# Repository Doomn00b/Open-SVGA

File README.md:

# Open-SVGA
Video-card and GPU for the PC x86 platform, including PCB reference-design

This project is meant to encompass a PCI 3.0 31-bits video-card capable of displaying the majority of resolutions and video-modes from CGA, EGA, VGA and finally SVGA. Drivers are meant to be developed for DoS 6.5, Windows 98SE and Windows 10.

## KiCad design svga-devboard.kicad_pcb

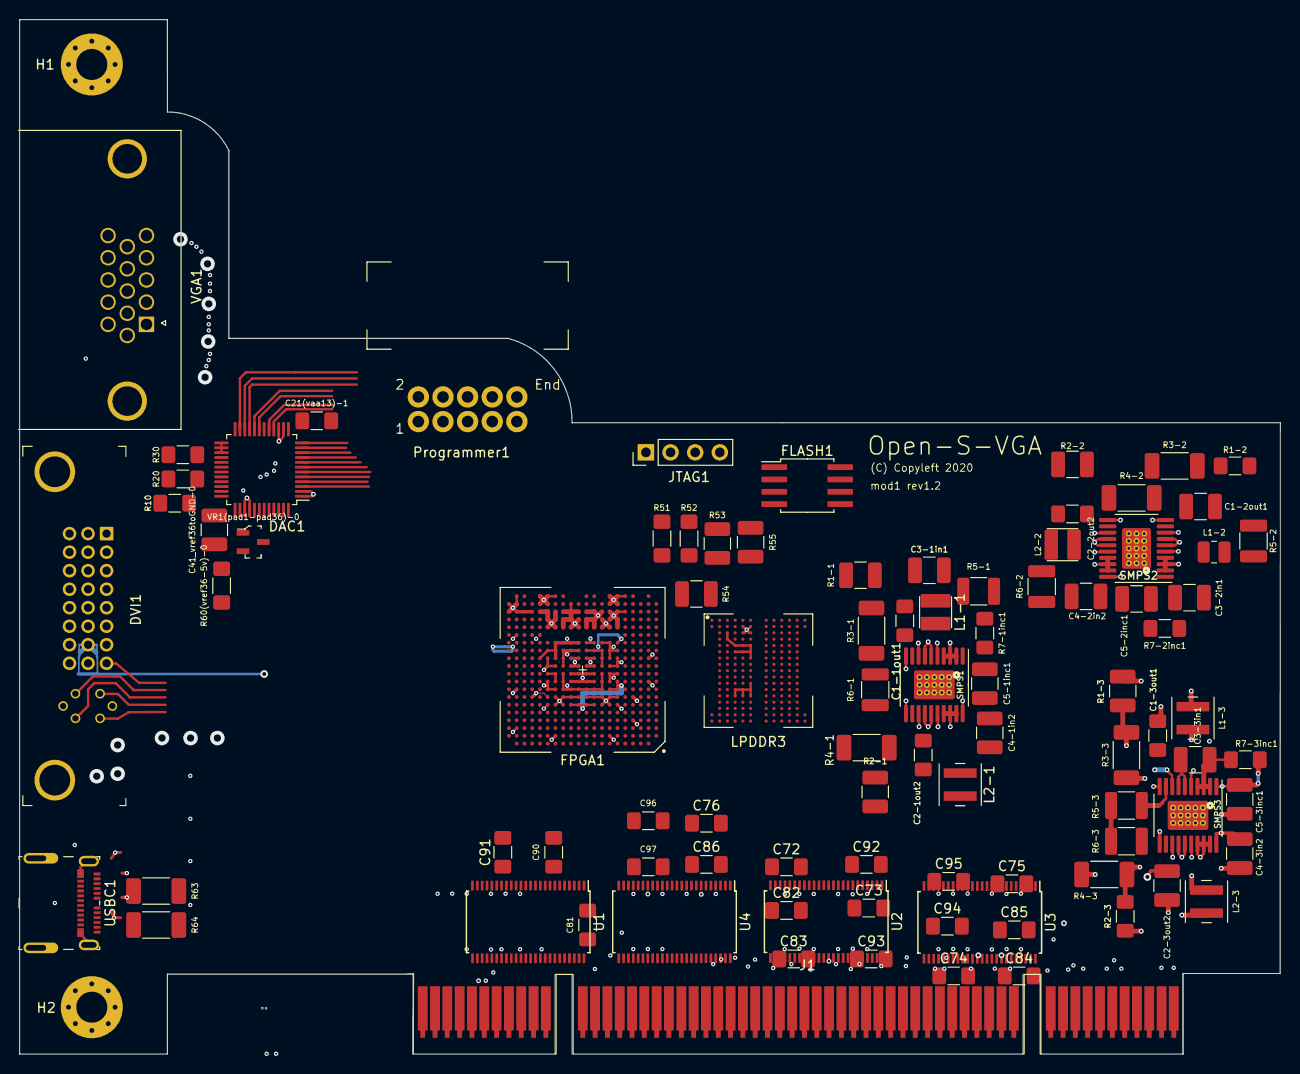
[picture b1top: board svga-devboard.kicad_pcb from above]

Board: 4 copper layers, 130.0 x 106.7 mm, 106 parts (0 on the bottom side), 146 nets.

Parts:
C1-1out1, C1-3out1, C2-1out2, C2-2out2: C3216X7S0J336M160AC; C_1206_3216Metric_Pad1.42x1.75mm_HandSolder
C1-2out1, C2-3out2: C3225X7R1C226M250AC; C_1210_3225Metric_Pad1.42x2.65mm_HandSolder
C3-1in1, C3-2in1, C3-3in1, C4-1in2, C4-2in2, C4-3in2, C41_vref36toGND-0: C1210C156K8PACTU; C_1210_3225Metric_Pad1.42x2.65mm_HandSolder
C5-1inc1, C5-2inc1, C5-3inc1: C1210C474K5RACTU; C_1210_3225Metric_Pad1.42x2.65mm_HandSolder
C10(vaa29)-0, C20(vaa13)-0, C30(vaa30)-0, C42(+5to35)1, C80, C81, C82, C83, C84, C85, C86, C87, C90, C91, C92, C93, C94, C95, C96, C97: VJ1206Y104JXAAR; C_1206_3216Metric_Pad1.42x1.75mm_HandSolder
C11(vaa29)-1, C21(vaa13)-1, C31(vaa30)-1: VJ1206Y103JXAMC; C_1206_3216Metric_Pad1.42x1.75mm_HandSolder
C70, C71, C72, C73, C74, C75, C76, C77: C1206C105K4RACTU; C_1206_3216Metric_Pad1.42x1.75mm_HandSolder
DAC1: ADV7125KSTZ50; LQFP-48_7x7mm_P0.5mm
DVI1: 74320-9010; DVI_Female_74320-9010
FLASH1: ISSI_IS25WP128F-JBLE; SOIC-8_5.28x5.28mm_P1.27mm
FPGA1: LFE5U-85F-BG381-LRJ; caBGA-381_15.2x15.2_17.0x17.0mm
H1, H2: MountingHole_Pad; MountingHole_3.2mm_M3_Pad_Via
J1: Bus_PCI_32bit_Universal_lrj; BUS_PCI_UNI_32-lrj2
JTAG1: CONN_04JST-PTH; PinHeader_1x04_P2.54mm_Vertical
L1-1, L2-2: VLS3015CX-1R5M-1; L_TDK_VLS3015CX-1_handsoldering
L1-2: 1008PS-152KLC; L_1008_2520Metric
L1-3, L2-1, L2-3: XFL4015-701MEC; L_Coilcraft_XFL4015
LPDDR3: W63CH2MBVACE; Winbond_VFBGA-178_W63CH2MBVACE
Programmer1: Wurth_WR-BHD_61201021721; WE_WR-BHD_RA_2x5_P2.54mm_Drill1.2mm
R1-1: CRCW121012K7FKEA; R_1210_3225Metric_Pad1.42x2.65mm_HandSolder
R1-2: ERJ-8ENF2152V; R_1206_3216Metric_Pad1.42x1.75mm_HandSolder
R1-3, R2-1: ERJ-14NF3741U; R_1210_3225Metric_Pad1.42x2.65mm_HandSolder
R2-2: RC1210FR-074K99L; R_1210_3225Metric_Pad1.42x2.65mm_HandSolder
R2-3, R7-1inc1, R7-2inc1, R7-3inc1: CRCW12064R99FKEAHP; R_1206_3216Metric_Pad1.42x1.75mm_HandSolder
R3-1, R3-2, R3-3, R4-1, R4-2, R4-3: CMP2010-FX-1002ELF; R_2010_5025Metric_Pad1.52x2.65mm_HandSolder
R5-1, R5-2, R5-3, R6-1, R6-2, R6-3: RC1210FR-0749K9L; R_YAGEO_1210_3225Metric_HandSolder
R10, R20, R30: CRCW120675R0FKEA; R_1206_3216Metric_Pad1.42x1.75mm_HandSolder
R51, R52: ERJ-8ENF4701V; R_Panasonic_1206_3216Metric_ERJ8EN_HandSolder
R53, R55: ERJ-14YJ103U; R_1210_3225Metric_Pad1.42x2.65mm_HandSolder
R54: RC1210FR-071KL; R_1210_3225Metric_Pad1.42x2.65mm_HandSolder
R60(vref36-5v)-0: ERJ-8ENF1001V; R_Panasonic_1206_3216Metric_ERJ8EN_HandSolder
R63, R64: CMP2010-FX-1004ELF; R_2010_5025Metric_Pad1.52x2.65mm_HandSolder
RZQ1: ERJ-8ENF2400V; R_Panasonic_1206_3216Metric_ERJ8EN_HandSolder
SMPS1, SMPS2, SMPS3: LM26420-Q1MHX_NOPB; HTSSOP-20-1EP_4.4x6.5mm_P0.42mm_EP3.2x6.4mm_Mask3.0x4.2mm_T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
U1, U2, U3, U4: SN74LVCH16T245DGGR; TSSOP-48_6.1x12.5mm_P0.5mm
USBC1: USB_C_Molex_201267-0005; USB-C_Receptacle_2012670005
VGA1: Amphenol_L77HDE15SD1CH4RHNVGA; DSUB-Amphenol_L77HDE15SD1CH4RHNVGA
VR1(pad1-pad36)-0: AD1580ARTZ-REEL7; SOT-23-3

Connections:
+0V8: C2-3out2.1, FPGA1.D20, L2-3.2, R2-3.2
+1V1: C1-3out1.1, C2-1out2.1, FPGA1.H8, FPGA1.H9, FPGA1.H10, FPGA1.H11, FPGA1.H12, FPGA1.H13, FPGA1.J8, FPGA1.J13, FPGA1.K8, FPGA1.K13, FPGA1.L8, FPGA1.L13, FPGA1.M8, FPGA1.M13, FPGA1.N8, FPGA1.N9, FPGA1.N10, FPGA1.N11, FPGA1.N12, FPGA1.N13, L1-3.1, L2-1.2, R1-3.1, R2-1.2
+1V2: C2-2out2.1, C90.1, C91.1, C92.1, C93.1, C94.1, C95.1, C96.1, C97.1, L2-2.2, LPDDR3.A8, LPDDR3.A9, LPDDR3.A11, LPDDR3.C12, LPDDR3.D4, LPDDR3.D5, LPDDR3.D6, LPDDR3.E8, LPDDR3.E12, LPDDR3.F2, LPDDR3.G2, LPDDR3.G5, LPDDR3.G12, LPDDR3.H3, LPDDR3.H5, LPDDR3.H6, LPDDR3.H8, LPDDR3.H9, LPDDR3.H11, LPDDR3.H12, LPDDR3.J5, LPDDR3.J6, LPDDR3.J9, LPDDR3.J10, LPDDR3.K5, LPDDR3.K6, LPDDR3.K8, LPDDR3.K11, LPDDR3.K12, LPDDR3.L2, LPDDR3.L5, LPDDR3.L12, LPDDR3.M2, LPDDR3.N8, LPDDR3.N12, LPDDR3.P4, LPDDR3.P5, LPDDR3.P6, LPDDR3.R12, LPDDR3.U8, LPDDR3.U9, LPDDR3.U11, R2-2.2, U1.7, U1.18, U2.7, U2.18, U3.7, U3.18, U4.7, U4.18
+1V8: C1-1out1.1, FLASH1.8, L1-1.1, LPDDR3.A3, LPDDR3.A4, LPDDR3.A5, LPDDR3.A6, LPDDR3.A10, LPDDR3.U3, LPDDR3.U4, LPDDR3.U5, LPDDR3.U6, LPDDR3.U10, R1-1.1
+2V5: C1-2out1.1, FLASH1.6, FPGA1.F6, FPGA1.F9, FPGA1.F10, FPGA1.F11, FPGA1.F12, FPGA1.F15, FPGA1.H6, FPGA1.H7, FPGA1.H14, FPGA1.H15, FPGA1.J6, FPGA1.J15, FPGA1.L6, FPGA1.L7, FPGA1.L14, FPGA1.L15, FPGA1.M6, FPGA1.M15, FPGA1.P6, FPGA1.P9, FPGA1.P10, FPGA1.T4, FPGA1.U3, L1-2.1, Programmer1.10, R1-2.1, R52.2, R53.2, R54.1, R54.2, R55.2, R64.2
+3V3: C3-1in1.2, C4-1in2.2, C4-2in2.2, C71.2, C73.2, C75.2, C77.2, C81.1, C83.1, C85.1, C87.1, J1.A21, J1.A27, J1.A33, J1.A39, J1.A45, J1.A53, J1.B25, J1.B31, J1.B36, J1.B41, J1.B43, J1.B54, R5-1.1, R6-1.1, R6-2.1, R7-1inc1.2, SMPS1.2, SMPS1.3, SMPS1.4, SMPS1.17, SMPS1.18, SMPS1.19, SMPS2.17, SMPS2.18, SMPS2.19, U1.42, U2.42, U3.42, U4.42
+5V: C3-2in1.2, C3-3in1.2, C4-3in2.2, C10(vaa29)-0.1, C11(vaa29)-1.1, C20(vaa13)-0.1, C21(vaa13)-1.1, C30(vaa30)-0.1, C31(vaa30)-1.1, C42(+5to35)1.1, C70.2, C72.2, C74.2, C76.2, C80.1, C82.1, C84.1, C86.1, DAC1.13, DAC1.29, DAC1.30, DVI1.14, J1.A5, J1.A8, J1.A61, J1.A62, J1.B5, J1.B6, J1.B61, J1.B62, R5-2.1, R5-3.1, R6-3.1, R7-2inc1.2, R7-3inc1.2, R60(vref36-5v)-0.1, SMPS2.2, SMPS2.3, SMPS2.4, SMPS3.2, SMPS3.3, SMPS3.4, SMPS3.17, SMPS3.18, SMPS3.19, U1.31, U2.31, U3.31, U4.31, USBC1.A4, USBC1.A9, USBC1.B4, USBC1.B9, VGA1.9
/DAC/ABLUE: DAC1.28, R30.2
/DAC/AGREEN: DAC1.32, R20.2
/DAC/ARED: DAC1.34, R10.2
/DAC/BLANK_DAC: DAC1.11, FPGA1.L18
/DAC/BLUE0: DAC1.16, FPGA1.P17
/DAC/BLUE1: DAC1.17, FPGA1.J16
/DAC/BLUE2: DAC1.18, FPGA1.T16
/DAC/BLUE3: DAC1.19, FPGA1.F16
/DAC/BLUE4: DAC1.20, FPGA1.U19
/DAC/BLUE5: DAC1.21, FPGA1.J18
/DAC/BLUE6: DAC1.22, FPGA1.H16
/DAC/BLUE7: DAC1.23, FPGA1.G16
/DAC/CLK_DAC: DAC1.24, FPGA1.P20
/DAC/GREEN0: DAC1.3, FPGA1.R17
/DAC/GREEN1: DAC1.4, FPGA1.R16
/DAC/GREEN2: DAC1.5, FPGA1.P19
/DAC/GREEN3: DAC1.6, FPGA1.P18
/DAC/GREEN4: DAC1.7, FPGA1.T18
/DAC/GREEN5: DAC1.8, FPGA1.K18
/DAC/GREEN6: DAC1.9, FPGA1.N18
/DAC/GREEN7: DAC1.10, FPGA1.U20
/DAC/RED0: DAC1.41, FPGA1.R20
/DAC/RED1: DAC1.42, FPGA1.E18
/DAC/RED2: DAC1.43, FPGA1.J17
/DAC/RED3: DAC1.44, FPGA1.J20
/DAC/RED4: DAC1.45, FPGA1.F18
/DAC/RED5: DAC1.46, FPGA1.F20
/DAC/RED6: DAC1.47, FPGA1.E16
/DAC/RED7: DAC1.48, FPGA1.K20
/DAC/SYNC_DAC: DAC1.12, FPGA1.E20
/DRAM/A0_DRAM: FPGA1.G5, LPDDR3.R2
/DRAM/A1_DRAM: FPGA1.C2, LPDDR3.P2
/DRAM/A2_DRAM: FPGA1.C3, LPDDR3.N2
/DRAM/A3_DRAM: FPGA1.B5, LPDDR3.N3
/DRAM/A4_DRAM: FPGA1.C5, LPDDR3.M3
/DRAM/A5_DRAM: FPGA1.J3, LPDDR3.F3
/DRAM/A6_DRAM: FPGA1.H3, LPDDR3.E3
/DRAM/A7_DRAM: FPGA1.G1, LPDDR3.E2
/DRAM/A8_DRAM: FPGA1.E5, LPDDR3.D2
/DRAM/A9_DRAM: FPGA1.F5, LPDDR3.C2
/DRAM/CKE_DRAM: FPGA1.H4, LPDDR3.K3
/DRAM/CK_t_DRAM: FPGA1.G3, LPDDR3.J3
/DRAM/D0_DRAM: FPGA1.M1, LPDDR3.P9
/DRAM/D1_DRAM: FPGA1.K2, LPDDR3.N9
/DRAM/D2_DRAM: FPGA1.M5, LPDDR3.N10
/DRAM/D3_DRAM: FPGA1.M3, LPDDR3.N11
/DRAM/D4_DRAM: FPGA1.J1, LPDDR3.M8
/DRAM/D5_DRAM: FPGA1.K5, LPDDR3.M9
/DRAM/D6_DRAM: FPGA1.K4, LPDDR3.M10
/DRAM/D7_DRAM: FPGA1.N3, LPDDR3.M11
/DRAM/D8_DRAM: FPGA1.P4, LPDDR3.F11
/DRAM/D9_DRAM: FPGA1.D2, LPDDR3.F10
/DRAM/D10_DRAM: FPGA1.D3, LPDDR3.F9
/DRAM/D11_DRAM: FPGA1.N2, LPDDR3.F8
/DRAM/D12_DRAM: FPGA1.P3, LPDDR3.E11
/DRAM/D13_DRAM: FPGA1.K1, LPDDR3.E10
/DRAM/D14_DRAM: FPGA1.L1, LPDDR3.E9
/DRAM/D15_DRAM: FPGA1.N1, LPDDR3.D9
/DRAM/D16_DRAM: FPGA1.E2, LPDDR3.T8
/DRAM/D17_DRAM: FPGA1.A3, LPDDR3.T9
/DRAM/D18_DRAM: FPGA1.E1, LPDDR3.T10
/DRAM/D19_DRAM: FPGA1.F2, LPDDR3.T11
/DRAM/D20_DRAM: FPGA1.H2, LPDDR3.R8
/DRAM/D21_DRAM: FPGA1.B3, LPDDR3.R9
/DRAM/D22_DRAM: FPGA1.B2, LPDDR3.R10
/DRAM/D23_DRAM: FPGA1.H1, LPDDR3.R11
/DRAM/D24_DRAM: FPGA1.L2, LPDDR3.C11
/DRAM/D25_DRAM: FPGA1.L3, LPDDR3.C10
/DRAM/D26_DRAM: FPGA1.N4, LPDDR3.C9
/DRAM/D27_DRAM: FPGA1.P5, LPDDR3.C8
/DRAM/D28_DRAM: FPGA1.H5, LPDDR3.B11
/DRAM/D29_DRAM: FPGA1.K3, LPDDR3.B10
/DRAM/D30_DRAM: FPGA1.L5, LPDDR3.B9
/DRAM/D31_DRAM: FPGA1.L4, LPDDR3.B8
/DRAM/DM0_DRAM: FPGA1.P1, LPDDR3.L8
/DRAM/DM1_DRAM: FPGA1.P2, LPDDR3.G8
/DRAM/DM2_DRAM: FPGA1.J4, LPDDR3.P8
/DRAM/DM3_DRAM: FPGA1.J5, LPDDR3.D8
/DRAM/DQS0c_DRAM: FPGA1.A5, LPDDR3.L11
/DRAM/DQS0t_DRAM: FPGA1.A4, LPDDR3.L10
/DRAM/DQS1c_DRAM: FPGA1.D1, LPDDR3.G11
/DRAM/DQS1t_DRAM: FPGA1.C1, LPDDR3.G10
/DRAM/DQS2c_DRAM: FPGA1.N5, LPDDR3.P11
/DRAM/DQS2t_DRAM: FPGA1.M4, LPDDR3.P10
/DRAM/DQS3c_DRAM: FPGA1.F1, LPDDR3.D11
/DRAM/DQS3t_DRAM: FPGA1.G2, LPDDR3.D10
/JTAG+Config/CSSPIN_FPGA: FLASH1.1, FPGA1.R2, Programmer1.7, R52.1
/JTAG+Config/DOUT_FPGA: FPGA1.R3, Programmer1.5
/JTAG+Config/INIT_FPGA: FPGA1.V3, Programmer1.3
/JTAG+Config/IO2_FPGA: FLASH1.3, FPGA1.Y2, Programmer1.6
/JTAG+Config/IO3_FPGA: FLASH1.7, FPGA1.W1, Programmer1.8
/JTAG+Config/MISO_FPGA: FLASH1.2, FPGA1.V2, Programmer1.4, R55.1
/JTAG+Config/MOSI_FPGA: FLASH1.5, FPGA1.W2, Programmer1.2, R53.1
/JTAG+Config/PROG_FPGA: FPGA1.W3, Programmer1.1
/JTAG+Config/TCK_FPGA: FPGA1.T5, JTAG1.1, R51.2
/JTAG+Config/TDI_FPGA: FPGA1.R5, JTAG1.2
/JTAG+Config/TDO_FPGA: FPGA1.V4, JTAG1.3
/JTAG+Config/TMS_FPGA: FPGA1.U5, JTAG1.4
/VGA + DVI + USBC/ABLUE: DVI1.C3, VGA1.3
/VGA + DVI + USBC/AGREEN: DVI1.C2, VGA1.2
/VGA + DVI + USBC/ARED: DVI1.C1, VGA1.1
/VGA + DVI + USBC/AUX+: R64.1, USBC1.A8
/VGA + DVI + USBC/AUX-: R63.1, USBC1.B8
/VGA + DVI + USBC/DBLUE+2: DVI1.13, USBC1.A11
/VGA + DVI + USBC/DBLUE-2: DVI1.12, USBC1.A10
/VGA + DVI + USBC/DDC-C_ID3: DVI1.6, VGA1.15
/VGA + DVI + USBC/DDC-D_ID1: DVI1.7, VGA1.12
/VGA + DVI + USBC/DGREEN+2: DVI1.5, USBC1.A2
/VGA + DVI + USBC/DGREEN-2: DVI1.4, USBC1.A3
/VGA + DVI + USBC/DRED+2: DVI1.21, USBC1.B11
/VGA + DVI + USBC/DRED-2: DVI1.20, USBC1.B10
/VGA + DVI + USBC/Hsync_A: DVI1.C4, VGA1.14
/VGA + DVI + USBC/Vsync_A: DVI1.8, VGA1.13
GND: C1-1out1.2, C1-2out1.2, C1-3out1.2, C2-1out2.2, C2-2out2.2, C2-3out2.2, C3-1in1.1, C3-2in1.1, C3-3in1.1, C4-1in2.1, C4-2in2.1, C4-3in2.1, C5-1inc1.2, C5-2inc1.2, C5-3inc1.2, C10(vaa29)-0.2, C11(vaa29)-1.2, C20(vaa13)-0.2, C21(vaa13)-1.2, C30(vaa30)-0.2, C31(vaa30)-1.2, C41_vref36toGND-0.1, C70.1, C71.1, C72.1, C73.1, C74.1, C75.1, C76.1, C77.1, C80.2, C81.2, C82.2, C83.2, C84.2, C85.2, C86.2, C87.2, C90.2, C91.2, C92.2, C93.2, C94.2, C95.2, C96.2, C97.2, DAC1.1, DAC1.2, DAC1.14, DAC1.15, DAC1.39, DAC1.40, DVI1.3, DVI1.11, DVI1.15, DVI1.19, DVI1.22, FLASH1.4, FPGA1.B7, FPGA1.B14, FPGA1.C19, FPGA1.D4, FPGA1.F7, FPGA1.F8, FPGA1.F13, FPGA1.F14, FPGA1.G4, FPGA1.G6, FPGA1.G7, FPGA1.G8, FPGA1.G9, FPGA1.G10, FPGA1.G11, FPGA1.G12, FPGA1.G13, FPGA1.G14, FPGA1.G15, FPGA1.G17, FPGA1.H19, FPGA1.J2, FPGA1.J7, FPGA1.J9, FPGA1.J10, FPGA1.J11, FPGA1.J12, FPGA1.J14, FPGA1.K6, FPGA1.K7, FPGA1.K9, FPGA1.K10, FPGA1.K11, FPGA1.K12, FPGA1.K14, FPGA1.K15, FPGA1.L9, FPGA1.L10, FPGA1.L11, FPGA1.L12, FPGA1.M2, FPGA1.M7, FPGA1.M9, FPGA1.M10, FPGA1.M11, FPGA1.M12, FPGA1.M14, FPGA1.M16, FPGA1.N6, FPGA1.N7, FPGA1.N14, FPGA1.N15, FPGA1.P7, FPGA1.P8, FPGA1.P11, FPGA1.P12, FPGA1.P13, FPGA1.P14, FPGA1.R4, FPGA1.R19, FPGA1.T6, FPGA1.T7, FPGA1.T8, FPGA1.T9, FPGA1.T10, FPGA1.T11, FPGA1.T12, FPGA1.T13, FPGA1.T14, FPGA1.T15, FPGA1.U4, FPGA1.U6, FPGA1.U7, FPGA1.U8, FPGA1.U9, FPGA1.U10, FPGA1.U11, FPGA1.U12, FPGA1.U13, FPGA1.U14, FPGA1.U15, FPGA1.V5, FPGA1.V6, FPGA1.V7, FPGA1.V8, FPGA1.V9, FPGA1.V10, FPGA1.V11, FPGA1.V12, FPGA1.V13, FPGA1.V14, FPGA1.V15, FPGA1.V16, FPGA1.V17, FPGA1.V18, FPGA1.V19, FPGA1.V20, FPGA1.W6, FPGA1.W7, FPGA1.W12, FPGA1.W15, FPGA1.W16, FPGA1.W19, FPGA1.W20, FPGA1.Y5, FPGA1.Y6, FPGA1.Y7, FPGA1.Y14, FPGA1.Y15, FPGA1.Y16, FPGA1.Y19, H2.1, J1.A18, J1.A24, J1.A30, J1.A35, J1.A37, J1.A42, J1.A48, J1.A56, J1.B3, J1.B15, J1.B17, J1.B22, J1.B28, J1.B34, J1.B46, J1.B57, LPDDR3.B2, LPDDR3.B5, LPDDR3.B6, LPDDR3.B12, LPDDR3.C3, LPDDR3.C5, LPDDR3.C6, LPDDR3.D3, LPDDR3.D12, LPDDR3.E4, LPDDR3.E5, LPDDR3.E6, LPDDR3.F4, LPDDR3.F5, LPDDR3.F6, LPDDR3.F12, LPDDR3.G3, LPDDR3.G4, LPDDR3.G6, LPDDR3.G9, LPDDR3.H2, LPDDR3.H10, LPDDR3.J4, LPDDR3.J12, LPDDR3.K2, LPDDR3.K10, LPDDR3.L6, LPDDR3.L9, LPDDR3.M4, LPDDR3.M5, LPDDR3.M6, LPDDR3.M12, LPDDR3.N4, LPDDR3.N5, LPDDR3.N6, LPDDR3.P3, LPDDR3.P12, LPDDR3.R4, LPDDR3.R5, LPDDR3.R6, LPDDR3.T2, LPDDR3.T3, LPDDR3.T4, LPDDR3.T5, LPDDR3.T6, LPDDR3.T12, Programmer1.9, R3-1.2, R3-2.2, R3-3.2, R4-1.2, R4-2.2, R4-3.2, R51.1, R63.2, RZQ1.1, SMPS1.6, SMPS1.7, SMPS1.10, SMPS1.11, SMPS1.14, SMPS1.15, SMPS1.20, SMPS2.6, SMPS2.7, SMPS2.10, SMPS2.11, SMPS2.14, SMPS2.15, SMPS2.20, SMPS3.6, SMPS3.7, SMPS3.10, SMPS3.11, SMPS3.14, SMPS3.15, SMPS3.20, U1.4, U1.10, U1.15, U1.21, U1.28, U1.34, U1.39, U1.45, U2.4, U2.10, U2.15, U2.21, U2.28, U2.34, U2.39, U2.45, U3.2, U3.3, U3.4, U3.10, U3.15, U3.21, U3.28, U3.34, U3.39, U3.45, U3.46, U3.47, U4.4, U4.10, U4.15, U4.21, U4.28, U4.34, U4.39, U4.45, USBC1.A1, USBC1.A12, USBC1.B1, USBC1.B12, USBC1.SH, VGA1.5, VR1(pad1-pad36)-0.2, VR1(pad1-pad36)-0.3
GNDA: DAC1.25, DAC1.26, DAC1.27, DAC1.31, DAC1.33, DVI1.C5, DVI1.SH, H1.1, R10.1, R20.1, R30.1, VGA1.0, VGA1.6, VGA1.7, VGA1.8, VGA1.16
unnamed: C5-1inc1.1, R7-1inc1.1, SMPS1.1
unnamed: C5-2inc1.1, R7-2inc1.1, SMPS2.1
unnamed: C5-3inc1.1, R7-3inc1.1, SMPS3.1
unnamed: C41_vref36toGND-0.2, DAC1.36, R60(vref36-5v)-0.2, VR1(pad1-pad36)-0.1
unnamed: C42(+5to35)1.2, DAC1.35
unnamed: L1-1.2, SMPS1.5
unnamed: L1-2.2, SMPS2.5
unnamed: L1-3.2, SMPS3.5
unnamed: L2-1.1, SMPS1.16
unnamed: L2-2.1, SMPS2.16
unnamed: L2-3.1, SMPS3.16
unnamed: LPDDR3.B3, RZQ1.2
unnamed: R1-1.2, R3-1.1, SMPS1.8
unnamed: R1-2.2, R3-2.1, SMPS2.8
unnamed: R1-3.2, R3-3.1, SMPS3.8
unnamed: R2-1.1, R4-1.1, SMPS1.13
unnamed: R2-2.1, R4-2.1, SMPS2.13
unnamed: R2-3.1, R4-3.1, SMPS3.13
unnamed: R5-1.2, SMPS1.9
unnamed: R5-2.2, SMPS2.9
unnamed: R5-3.2, SMPS3.9
unnamed: R6-1.2, SMPS1.12
unnamed: R6-2.2, SMPS2.12
unnamed: R6-3.2, SMPS3.12

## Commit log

2020-09-03 Add files via upload
    Listing of various refresh rates and the associated resolutions for them.
2020-09-03 Add files via upload
    Schematics in Kicad-format for the development-board prototype. Subject to constant change.
2020-09-03 Add files via upload
    Spreadsheets for selecting the most suitable VRAM-modules for the project. The memory-chips are sorted via a points-system, based on pre-requisites like power consumption, clock cycles, CAS delay, an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
2020-09-03 Add files via upload
    A file listing the 381 pins of the Lattice ECP5-85 FPGA that sits at the core of the project. The purpose is to make a visual guide to help make understanding and utilizing the FPGA easier, and to us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
2020-09-03 Add files via upload
    Main design-document collecting as many and varied a topic as the design-specifications, performance-targets, to-do-lists, reference-materials and other assorted information.
2020-09-28 Add files via upload
    Converted to hierarchical scheets, added support-components for SMPS-units - many other changes.
2020-10-17 Add files via upload
    Added Pull-up and pull-down resistors for JTAG and sysConfig connections.
    Added pinheaders for FPGA-Configuration. (replacing edge-connector)
    Combined the DVI+VGA and USB-C hierarchical sheets into one.
    Assigned a dedicated sheet for the DAC.
    Added 75 Ohm terminal-resistors to output of DAC.
    Placed filtering-capacitors for DAC VAA.
2023-07-09 Converted the project over to Kicad 7, and fixed all of the artifacts that came with it, such as updating symbols and footprints.
2023-07-21 Disconnected the DVI-connectors from each other, so that they do go over the intended flat-cable to the daughter-board instead.

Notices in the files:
svga-devboard.kicad_pcb:
(C) Copyleft 2020
